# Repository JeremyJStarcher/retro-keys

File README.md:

# retro-keys
Retro Keyboards for emulators

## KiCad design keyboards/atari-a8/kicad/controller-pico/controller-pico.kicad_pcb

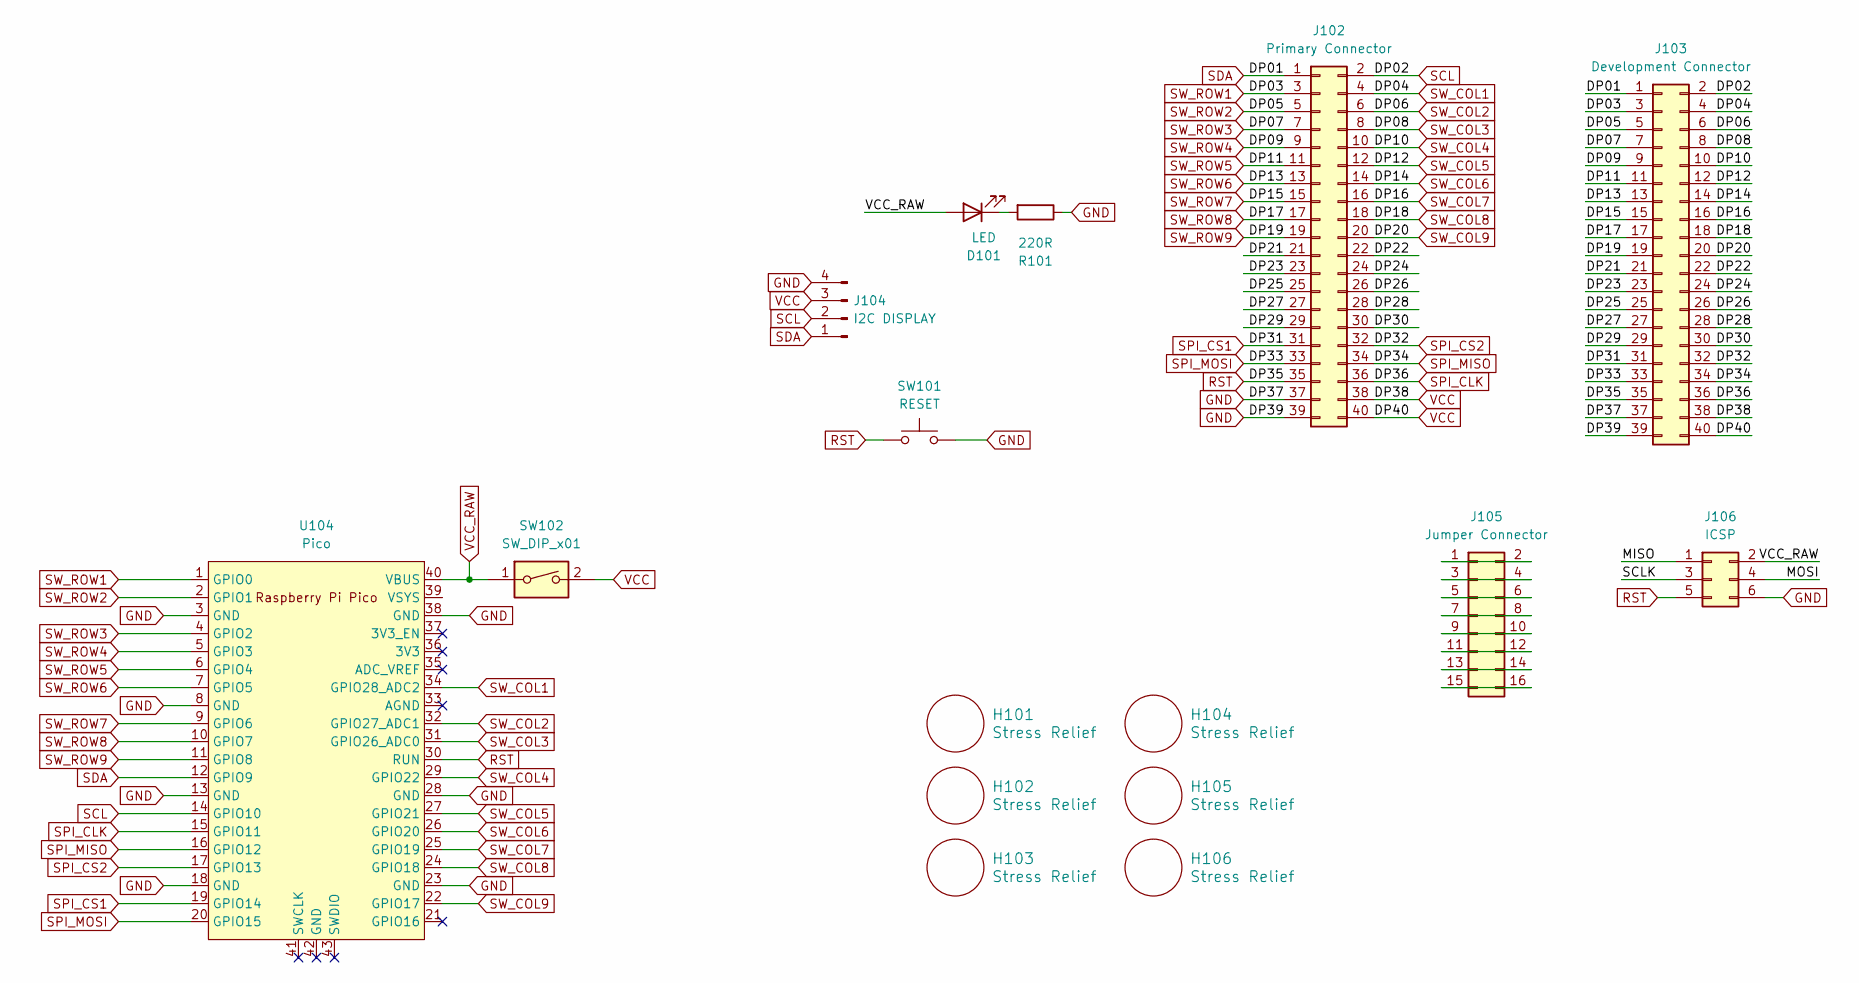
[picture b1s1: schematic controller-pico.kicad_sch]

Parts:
D101: LED; LED_D3.0mm
H101, H102, H103, H104, H105, H106: Stress Relief; MountingHole_2.7mm
J102: Primary Connector; PinHeader_2x20_P2.54mm_Vertical
J103: Development Connector; PinHeader_2x20_P2.54mm_Vertical
J104: I2C DISPLAY; PinHeader_1x04_P2.54mm_Horizontal
J105: Jumper Connector; PinHeader_2x08_P2.54mm_Vertical
J106: ICSP; PinHeader_2x03_P2.54mm_Vertical
R101: 220R; Resistor-Hybrid
SW101: RESET; SW_PUSH_6mm
SW102: SW_DIP_x01; SW_DIP_SPSTx01_Slide_9.78x4.72mm_W7.62mm_P2.54mm
U104: Pico; RPi_Pico_SMD_TH

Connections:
/DP21: J102.21, J103.21
/DP22: J102.22, J103.22
/DP23: J102.23, J103.23
/DP24: J102.24, J103.24
/DP25: J102.25, J103.25
/DP26: J102.26, J103.26
/DP27: J102.27, J103.27
/DP28: J102.28, J103.28
/DP29: J102.29, J103.29
/DP30: J102.30, J103.30
/MISO: J106.1
/MOSI: J106.4
/SCLK: J106.3
GND: J102.37, J102.39, J103.37, J103.39, J104.4, J106.6, R101.1, SW101.2, U104.3 (GND), U104.8 (GND), U104.13 (GND), U104.18 (GND), U104.23 (GND), U104.28 (GND), U104.38 (GND)
unnamed: D101.1 (K), R101.2
unnamed: J105.1, J105.2
unnamed: J105.3, J105.4
unnamed: J105.5, J105.6
unnamed: J105.7, J105.8
unnamed: J105.9, J105.10
unnamed: J105.11, J105.12
unnamed: J105.13, J105.14
unnamed: J105.15, J105.16
RST: J102.35, J103.35, J106.5, SW101.1, U104.30 (RUN)
SCL: J102.2, J103.2, J104.2, U104.14 (GPIO10)
SDA: J102.1, J103.1, J104.1, U104.12 (GPIO9)
SPI_CLK: J102.36, J103.36, U104.15 (GPIO11)
SPI_CS1: J102.31, J103.31, U104.19 (GPIO14)
SPI_CS2: J102.32, J103.32, U104.17 (GPIO13)
SPI_MISO: J102.34, J103.34, U104.16 (GPIO12)
SPI_MOSI: J102.33, J103.33, U104.20 (GPIO15)
SW_COL1: J102.4, J103.4, U104.34 (GPIO28_ADC2)
SW_COL2: J102.6, J103.6, U104.32 (GPIO27_ADC1)
SW_COL3: J102.8, J103.8, U104.31 (GPIO26_ADC0)
SW_COL4: J102.10, J103.10, U104.29 (GPIO22)
SW_COL5: J102.12, J103.12, U104.27 (GPIO21)
SW_COL6: J102.14, J103.14, U104.26 (GPIO20)
SW_COL7: J102.16, J103.16, U104.25 (GPIO19)
SW_COL8: J102.18, J103.18, U104.24 (GPIO18)
SW_COL9: J102.20, J103.20, U104.22 (GPIO17)
SW_ROW1: J102.3, J103.3, U104.1 (GPIO0)
SW_ROW2: J102.5, J103.5, U104.2 (GPIO1)
SW_ROW3: J102.7, J103.7, U104.4 (GPIO2)
SW_ROW4: J102.9, J103.9, U104.5 (GPIO3)
SW_ROW5: J102.11, J103.11, U104.6 (GPIO4)
SW_ROW6: J102.13, J103.13, U104.7 (GPIO5)
SW_ROW7: J102.15, J103.15, U104.9 (GPIO6)
SW_ROW8: J102.17, J103.17, U104.10 (GPIO7)
SW_ROW9: J102.19, J103.19, U104.11 (GPIO8)
VCC: J102.38, J102.40, J103.38, J103.40, J104.3, SW102.2
VCC_RAW: D101.2 (A), J106.2, SW102.1, U104.40 (VBUS)

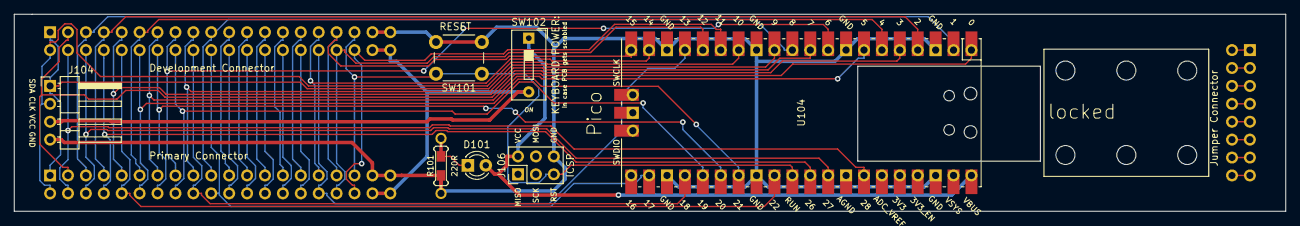
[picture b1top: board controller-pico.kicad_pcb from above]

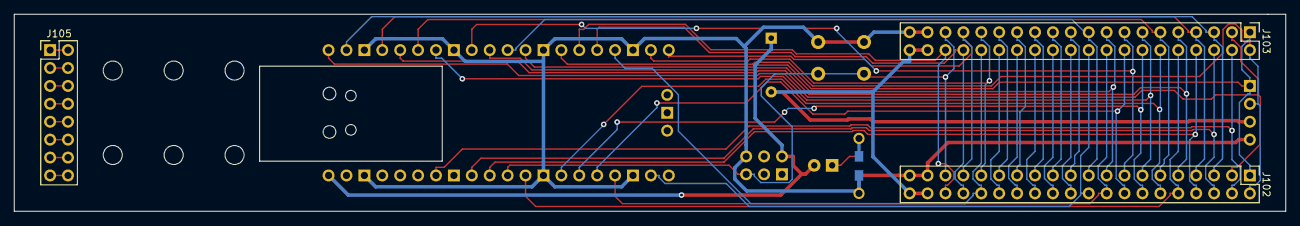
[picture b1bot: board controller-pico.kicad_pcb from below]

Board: 2 copper layers, 180.3 x 27.9 mm, 16 parts (3 on the bottom side), 48 nets.

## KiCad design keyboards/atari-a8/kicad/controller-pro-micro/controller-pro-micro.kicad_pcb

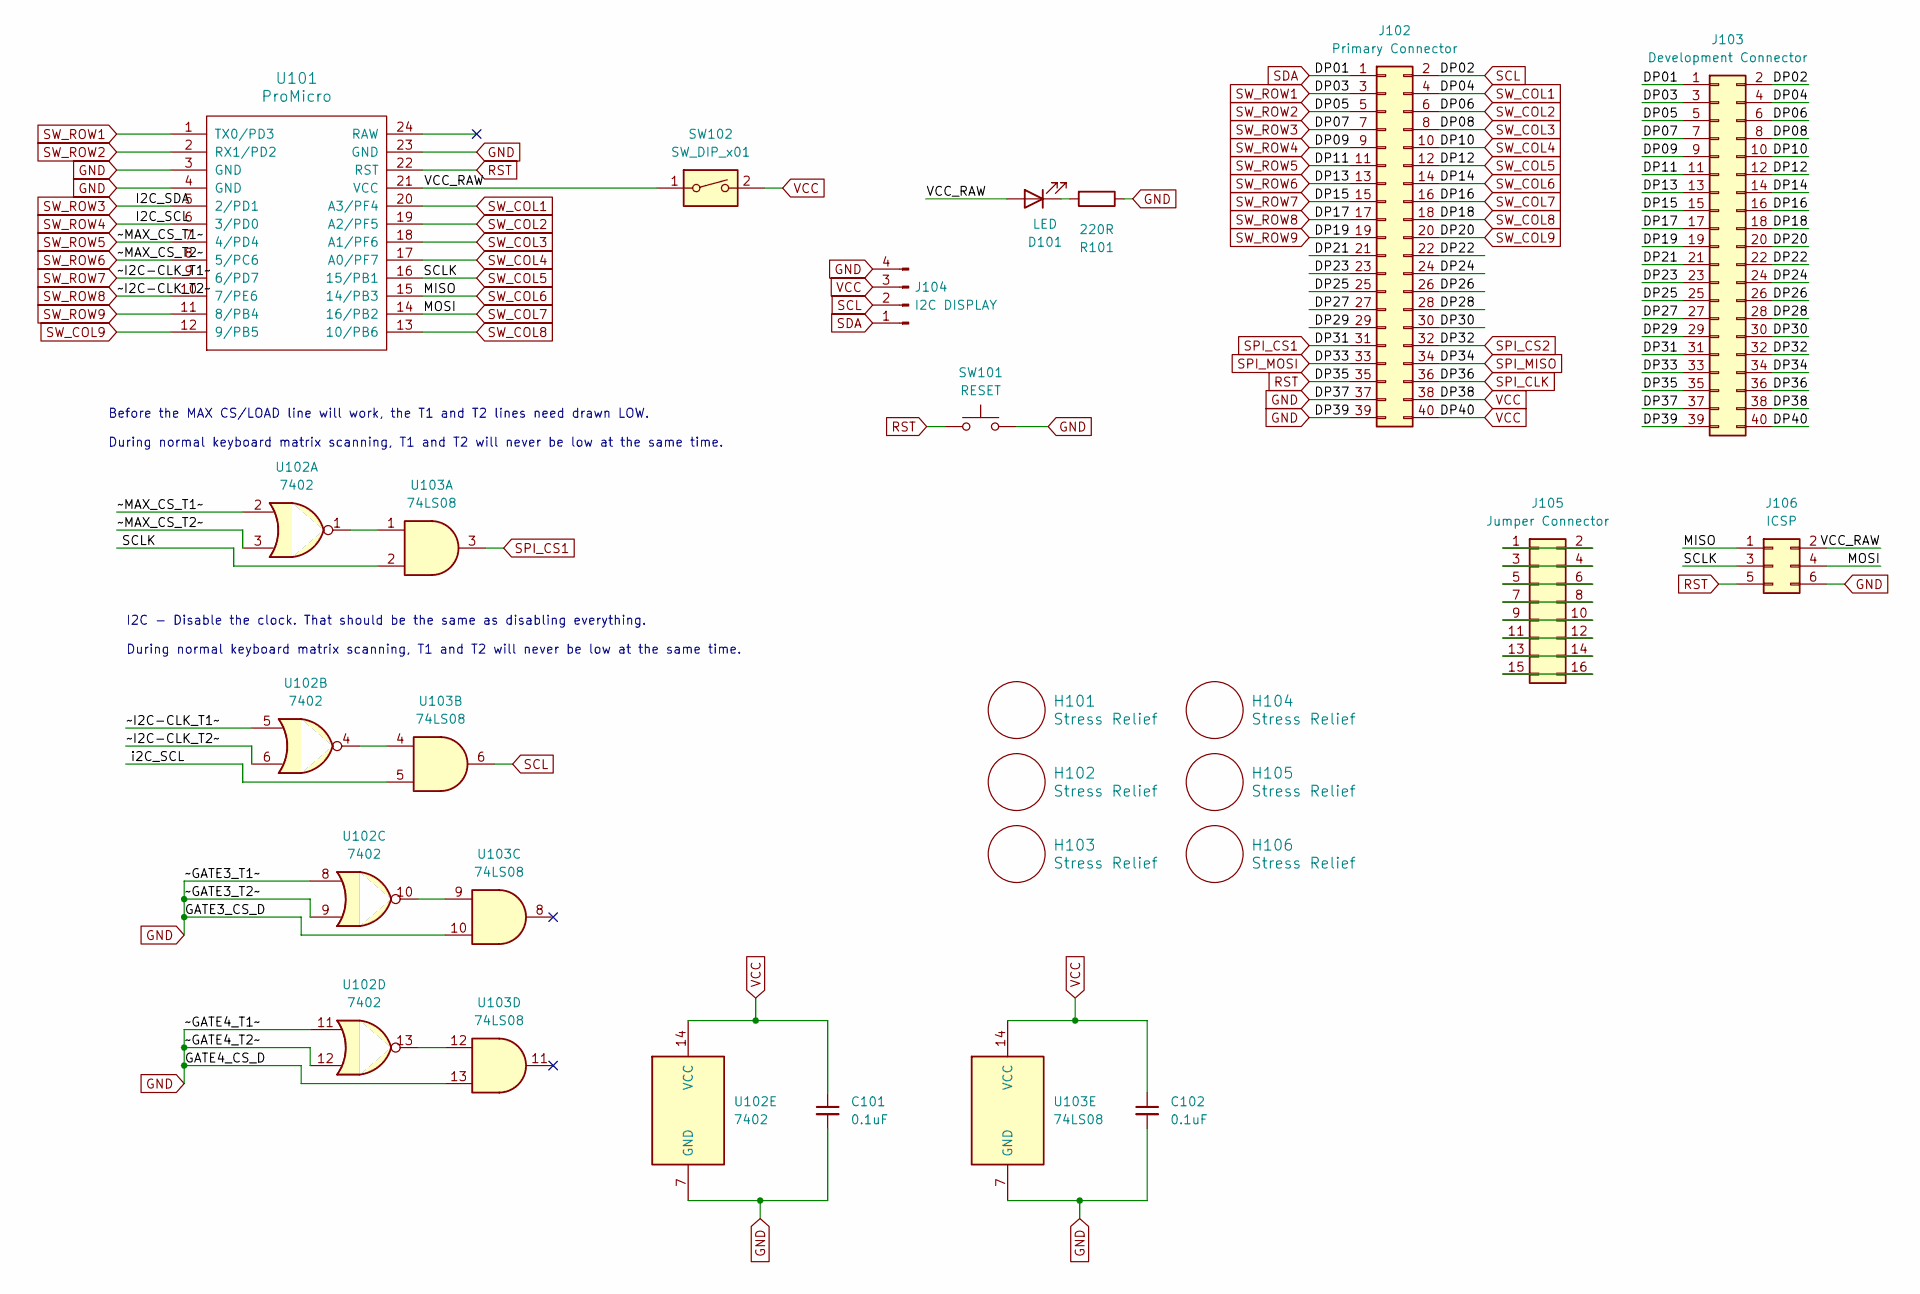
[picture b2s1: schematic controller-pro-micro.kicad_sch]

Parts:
C101, C102: 0.1uF; C_Axial_L3.8mm_D2.6mm_P7.50mm_Horizontal
D101: LED; LED_D3.0mm
H101, H102, H103, H104, H105, H106: Stress Relief; MountingHole_2.7mm
J102: Primary Connector; PinHeader_2x20_P2.54mm_Vertical
J103: Development Connector; PinHeader_2x20_P2.54mm_Vertical
J104: I2C DISPLAY; PinHeader_1x04_P2.54mm_Horizontal
J105: Jumper Connector; PinHeader_2x08_P2.54mm_Vertical
J106: ICSP; PinHeader_2x03_P2.54mm_Vertical
R101: 220R; Resistor-Hybrid
SW101: RESET; SW_PUSH_6mm
SW102: SW_DIP_x01; SW_DIP_SPSTx01_Slide_9.78x4.72mm_W7.62mm_P2.54mm
U101: ProMicro
U102: 7402; DIP-14_W7.62mm_Socket
U103: 74LS08; DIP-14_W7.62mm_Socket

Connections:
/DP21: J102.21, J103.21
/DP22: J102.22, J103.22
/DP23: J102.23, J103.23
/DP24: J102.24, J103.24
/DP25: J102.25, J103.25
/DP26: J102.26, J103.26
/DP27: J102.27, J103.27
/DP28: J102.28, J103.28
/DP29: J102.29, J103.29
/DP30: J102.30, J103.30
/VCC_RAW: D101.2 (A), J106.2, SW102.1, U101.21 (VCC)
/i2C_SCL: U103.5
GND: C101.2, C102.2, J102.37, J102.39, J103.37, J103.39, J104.4, J106.6, R101.1, SW101.2, U101.3 (GND), U101.4 (GND), U101.23 (GND), U102.7 (GND), U102.8, U102.9, U102.11, U102.12, U103.7 (GND), U103.10, U103.13
unnamed: D101.1 (K), R101.2
unnamed: J105.1, J105.2
unnamed: J105.3, J105.4
unnamed: J105.5, J105.6
unnamed: J105.7, J105.8
unnamed: J105.9, J105.10
unnamed: J105.11, J105.12
unnamed: J105.13, J105.14
unnamed: J105.15, J105.16
unnamed: U102.1, U103.1
unnamed: U102.4, U103.4
unnamed: U102.10, U103.9
unnamed: U102.13, U103.12
RST: J102.35, J103.35, J106.5, SW101.1, U101.22 (RST)
SCL: J102.2, J103.2, J104.2, U103.6
SDA: J102.1, J103.1, J104.1
SPI_CLK: J102.36, J103.36
SPI_CS1: J102.31, J103.31, U103.3
SPI_CS2: J102.32, J103.32
SPI_MISO: J102.34, J103.34
SPI_MOSI: J102.33, J103.33
SW_COL1: J102.4, J103.4, U101.20 (A3/PF4)
SW_COL2: J102.6, J103.6, U101.19 (A2/PF5)
SW_COL3: J102.8, J103.8, U101.18 (A1/PF6)
SW_COL4: J102.10, J103.10, U101.17 (A0/PF7)
SW_COL5: J102.12, J103.12, J106.3, U101.16 (15/PB1), U103.2
SW_COL6: J102.14, J103.14, J106.1, U101.15 (14/PB3)
SW_COL7: J102.16, J103.16, J106.4, U101.14 (16/PB2)
SW_COL8: J102.18, J103.18, U101.13 (10/PB6)
SW_COL9: J102.20, J103.20, U101.12 (9/PB5)
SW_ROW1: J102.3, J103.3, U101.1 (TX0/PD3)
SW_ROW2: J102.5, J103.5, U101.2 (RX1/PD2)
SW_ROW3: J102.7, J103.7, U101.5 (2/PD1)
SW_ROW4: J102.9, J103.9, U101.6 (3/PD0)
SW_ROW5: J102.11, J103.11, U101.7 (4/PD4), U102.2
SW_ROW6: J102.13, J103.13, U101.8 (5/PC6), U102.3
SW_ROW7: J102.15, J103.15, U101.9 (6/PD7), U102.5
SW_ROW8: J102.17, J103.17, U101.10 (7/PE6), U102.6
SW_ROW9: J102.19, J103.19, U101.11 (8/PB4)
VCC: C101.1, C102.1, J102.38, J102.40, J103.38, J103.40, J104.3, SW102.2, U102.14 (VCC), U103.14 (VCC)

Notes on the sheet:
I2C - Disable the clock. That should be the same as disabling everything. During normal keyboard matrix scanning, T1 and T2 will never be low at the same time.
Before the MAX CS/LOAD line will work, the T1 and T2 lines need drawn LOW. During normal keyboard matrix scanning, T1 and T2 will never be low at the same time.

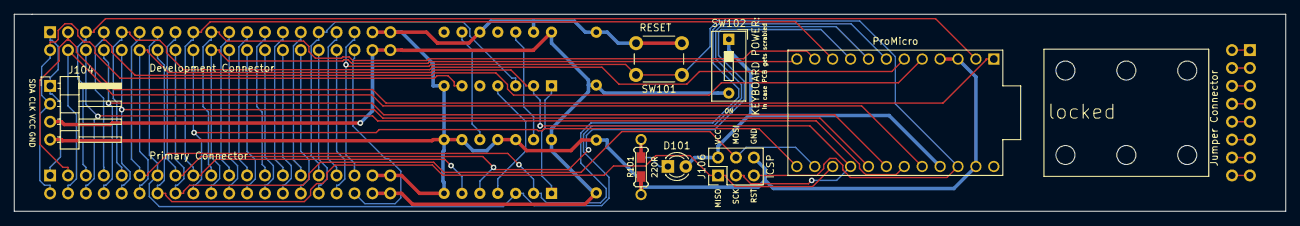
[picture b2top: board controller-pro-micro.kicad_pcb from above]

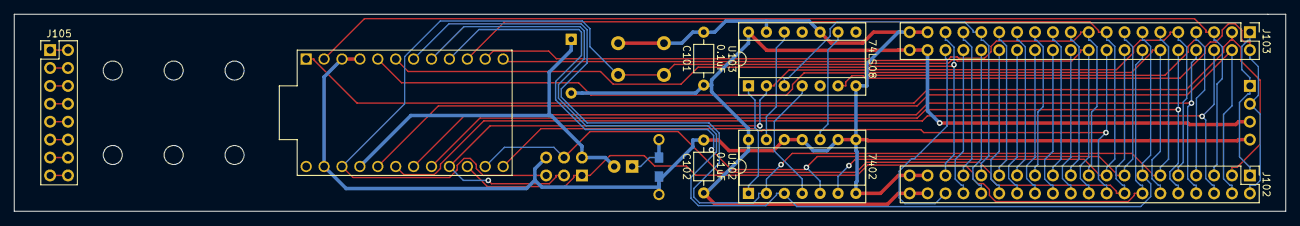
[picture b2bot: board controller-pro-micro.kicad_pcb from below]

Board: 2 copper layers, 180.3 x 27.9 mm, 20 parts (7 on the bottom side), 52 nets.

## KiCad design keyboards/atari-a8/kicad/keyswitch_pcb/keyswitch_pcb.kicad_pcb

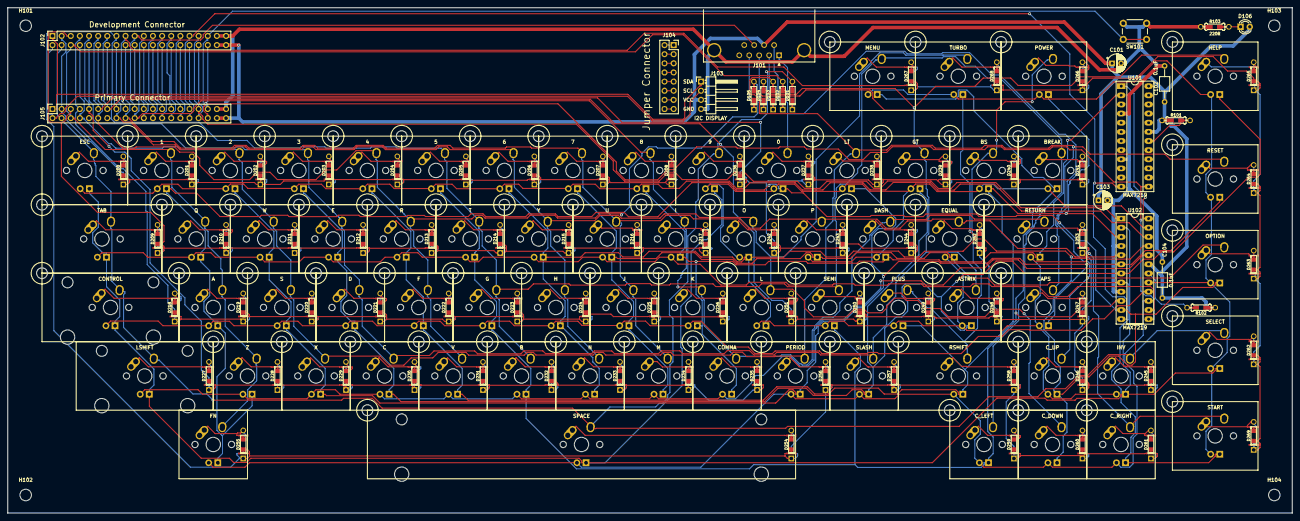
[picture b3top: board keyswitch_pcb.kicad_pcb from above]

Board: 2 copper layers, 357.2 x 140.5 mm, 165 parts (0 on the bottom side), 142 nets.

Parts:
C101, C103: 47uF; CP_Radial_D5.0mm_P2.50mm
C102, C104: 0.1uF; C_Axial_L3.8mm_D2.6mm_P10.00mm_Horizontal
D101: JS1_UP; Diode-dual
D102: JS1_TRIG; Diode-dual
D103: JS1_DOWN; Diode-dual
D104: JS1_LEFT; Diode-dual
D105: JS1_RIGHT; Diode-dual
D106: LED; LED_D3.0mm
D200: ESC; Diode-dual
D201: 1; Diode-dual
D202: 2; Diode-dual
D203: 3; Diode-dual
D204: 4; Diode-dual
D205: 5; Diode-dual
D206: 6; Diode-dual
D207: 7; Diode-dual
D208: 8; Diode-dual
D209: TAB; Diode-dual
D210: Q; Diode-dual
D211: W; Diode-dual
D212: E; Diode-dual
D213: R; Diode-dual
D214: T; Diode-dual
D215: Y; Diode-dual
D216: U; Diode-dual
D217: I; Diode-dual
D218: CONTROL; Diode-dual
D219: A; Diode-dual
D220: S; Diode-dual
D221: D; Diode-dual
D222: F; Diode-dual
D223: G; Diode-dual
D224: H; Diode-dual
D225: J; Diode-dual
D226: K; Diode-dual
D227: LSHIFT; Diode-dual
D228: Z; Diode-dual
D229: X; Diode-dual
D230: C; Diode-dual
D231: V; Diode-dual
D232: B; Diode-dual
D233: N; Diode-dual
D234: M; Diode-dual
D235: COMMA; Diode-dual
D236: 9; Diode-dual
D237: 0; Diode-dual
D238: LT; Diode-dual
D239: GT; Diode-dual
D240: BS; Diode-dual
D241: BREAK; Diode-dual
D242: O; Diode-dual
D243: P; Diode-dual
D244: DASH; Diode-dual
D245: INV; Diode-dual
D246: C_UP; Diode-dual
D247: CAPS; Diode-dual
D248: ASTRIX; Diode-dual
D249: PLUS; Diode-dual
D250: SEMI; Diode-dual
D251: L; Diode-dual
D252: EQUAL; Diode-dual
D253: RETURN; Diode-dual
D254: SPACE; Diode-dual
D255: FN; Diode-dual
D256: PERIOD; Diode-dual
D257: SLASH; Diode-dual
D258: RSHIFT; Diode-dual
D259: C_LEFT; Diode-dual
D260: C_DOWN; Diode-dual
D261: C_RIGHT; Diode-dual
D262: SELECT; Diode-dual
D263: OPTION; Diode-dual
D264: RESET; Diode-dual
D265: HELP; Diode-dual
D266: POWER; Diode-dual
D267: MENU; Diode-dual
D268: TURBO; Diode-dual
D269: START; Diode-dual
H101, H102, H103, H104: MountingHole; MountingHole_3.2mm_M3
J101: PLAYER 1; DSUB-9_Male_Horizontal_P2.77x2.84mm_EdgePinOffset9.90mm_Hou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
J102: Development Connector; PinSocket_2x20_P2.54mm_Vertical
J103: I2C DISPLAY; PinHeader_1x04_P2.54mm_Horizontal
J104: Jumper Connector; PinSocket_2x08_P2.54mm_Vertical
J105: Primary Connector; PinSocket_2x20_P2.54mm_Vertical
R101, R102: 22K; Resistor-Hybrid
R103: 220R; Resistor-Hybrid
SW101: RESET; SW_PUSH_6mm
SW200: ESC; MX-1.25U
SW201: 1; MX-1U
SW202: 2; MX-1U
SW203: 3; MX-1U
SW204: 4; MX-1U
SW205: 5; MX-1U
SW206: 6; MX-1U
SW207: 7; MX-1U
SW208: 8; MX-1U
SW209: TAB; MX-1.75U
SW210: Q; MX-1U
SW211: W; MX-1U
SW212: E; MX-1U
SW213: R; MX-1U
SW214: T; MX-1U
SW215: Y; MX-1U
SW216: U; MX-1U
SW217: I; MX-1U
SW218: CONTROL; MX-2U
SW219: A; MX-1U
SW220: S; MX-1U
SW221: D; MX-1U
SW222: F; MX-1U
SW223: G; MX-1U
SW224: H; MX-1U
SW225: J; MX-1U
SW226: K; MX-1U
SW227: LSHIFT; MX-2U
SW228: Z; MX-1U
SW229: X; MX-1U
SW230: C; MX-1U
SW231: V; MX-1U
SW232: B; MX-1U
SW233: N; MX-1U
SW234: M; MX-1U
SW235: COMMA; MX-1U
SW236: 9; MX-1U
SW237: 0; MX-1U
SW238: LT; MX-1U
SW239: GT; MX-1U
SW240: BS; MX-1U
SW241: BREAK; MX-1U
SW242: O; MX-1U
SW243: P; MX-1U
SW244: DASH; MX-1U
SW245: INV; MX-1U
SW246: C_UP; MX-1U
SW247: CAPS; MX-1.25U
SW248: ASTRIX; MX-1U
SW249: PLUS; MX-1U
SW250: SEMI; MX-1U
SW251: L; MX-1U
SW252: EQUAL; MX-1U
SW253: RETURN; MX-1.5U
SW254: SPACE; MX-6.25U
SW255: FN; MX-1U
SW256: PERIOD; MX-1U
SW257: SLASH; MX-1U
SW258: RSHIFT; MX-1.75U
SW259: C_LEFT; MX-1U
SW260: C_DOWN; MX-1U
SW261: C_RIGHT; MX-1U
SW262: SELECT; MX-1.25U
SW263: OPTION; MX-1.25U
SW264: RESET; MX-1.25U
SW265: HELP; MX-1.25U
SW266: POWER; MX-1.25U
SW267: MENU; MX-1.25U
SW268: TURBO; MX-1.25U
SW269: START; MX-1.25U
U101, U102: MAX7219; DIP-24_W7.62mm_Socket_LongPads

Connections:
/DP21: J102.21, J105.21
/DP22: J102.22, J105.22
/DP23: J102.23, J105.23
/DP24: J102.24, J105.24
/DP25: J102.25, J105.25
/DP26: J102.26, J105.26
/DP27: J102.27, J105.27
/DP28: J102.28, J105.28
/DP29: J102.29, J105.29
/DP30: J102.30, J105.30
/SPI_D2: U101.1 (DIN), U102.24 (DOUT)
GND: C101.2, C102.2, C103.2, C104.2, J101.0 (GND), J102.37, J102.39, J103.4, J105.37, J105.39, R103.1, SW101.2, U101.4 (GND), U101.9 (GND), U102.4 (GND), U102.9 (GND)
LED_COL1: SW200.4, SW209.4, SW218.4, SW227.4, SW236.4, SW245.4, SW254.4, SW262.4, U102.2 (DIG_0)
LED_COL2: SW201.4, SW210.4, SW219.4, SW228.4, SW237.4, SW246.4, SW255.4, SW263.4, U102.11 (DIG_1)
LED_COL3: SW202.4, SW211.4, SW220.4, SW229.4, SW238.4, SW247.4, SW256.4, SW264.4, U102.6 (DIG_2)
LED_COL4: SW203.4, SW212.4, SW221.4, SW230.4, SW239.4, SW248.4, SW257.4, SW265.4, U102.7 (DIG_3)
LED_COL5: SW204.4, SW213.4, SW222.4, SW231.4, SW240.4, SW249.4, SW258.4, SW266.4, U102.3 (DIG_4)
LED_COL6: SW205.4, SW214.4, SW223.4, SW232.4, SW241.4, SW250.4, SW259.4, SW267.4, U102.10 (DIG_5)
LED_COL7: SW206.4, SW215.4, SW224.4, SW233.4, SW242.4, SW251.4, SW260.4, SW268.4, U102.5 (DIG_6)
LED_COL8: SW207.4, SW216.4, SW225.4, SW234.4, SW243.4, SW252.4, SW261.4, SW269.4, U102.8 (DIG_7)
LED_COL9: SW208.4, SW217.4, SW226.4, SW235.4, SW244.4, SW253.4, U101.2 (DIG_0)
LED_ROW1: SW200.3, SW201.3, SW202.3, SW203.3, SW204.3, SW205.3, SW206.3, SW207.3, SW208.3, U102.22 (SEG_DP)
LED_ROW2: SW209.3, SW210.3, SW211.3, SW212.3, SW213.3, SW214.3, SW215.3, SW216.3, SW217.3, U102.14 (SEG_A)
LED_ROW3: SW218.3, SW219.3, SW220.3, SW221.3, SW222.3, SW223.3, SW224.3, SW225.3, SW226.3, U102.16 (SEG_B)
LED_ROW4: SW227.3, SW228.3, SW229.3, SW230.3, SW231.3, SW232.3, SW233.3, SW234.3, SW235.3, U102.20 (SEG_C)
LED_ROW5: SW236.3, SW237.3, SW238.3, SW239.3, SW240.3, SW241.3, SW242.3, SW243.3, SW244.3, U102.23 (SEG_D)
LED_ROW6: SW245.3, SW246.3, SW247.3, SW248.3, SW249.3, SW250.3, SW251.3, SW252.3, SW253.3, U102.21 (SEG_E)
LED_ROW7: SW254.3, SW255.3, SW256.3, SW257.3, SW258.3, SW259.3, SW260.3, SW261.3, U102.15 (SEG_F)
LED_ROW8: SW262.3, SW263.3, SW264.3, SW265.3, SW266.3, SW267.3, SW268.3, SW269.3, U102.17 (SEG_G)
unnamed: D101.1 (K), J101.1
unnamed: D102.1 (K), J101.6
unnamed: D103.1 (K), J101.2
unnamed: D104.1 (K), J101.3
unnamed: D105.1 (K), J101.4
unnamed: D106.1 (K), R103.2
unnamed: D200.2 (A), SW200.1
unnamed: D201.2 (A), SW201.1
unnamed: D202.2 (A), SW202.1
unnamed: D203.2 (A), SW203.1
unnamed: D204.2 (A), SW204.1
unnamed: D205.2 (A), SW205.1
unnamed: D206.2 (A), SW206.1
unnamed: D207.2 (A), SW207.1
unnamed: D208.2 (A), SW208.1
unnamed: D209.2 (A), SW209.1
unnamed: D210.2 (A), SW210.1
unnamed: D211.2 (A), SW211.1
unnamed: D212.2 (A), SW212.1
unnamed: D213.2 (A), SW213.1
unnamed: D214.2 (A), SW214.1
unnamed: D215.2 (A), SW215.1
unnamed: D216.2 (A), SW216.1
unnamed: D217.2 (A), SW217.1
unnamed: D218.2 (A), SW218.1
unnamed: D219.2 (A), SW219.1
unnamed: D220.2 (A), SW220.1
unnamed: D221.2 (A), SW221.1
unnamed: D222.2 (A), SW222.1
unnamed: D223.2 (A), SW223.1
unnamed: D224.2 (A), SW224.1
unnamed: D225.2 (A), SW225.1
unnamed: D226.2 (A), SW226.1
unnamed: D227.2 (A), SW227.1
unnamed: D228.2 (A), SW228.1
unnamed: D229.2 (A), SW229.1
unnamed: D230.2 (A), SW230.1
unnamed: D231.2 (A), SW231.1
unnamed: D232.2 (A), SW232.1
unnamed: D233.2 (A), SW233.1
unnamed: D234.2 (A), SW234.1
unnamed: D235.2 (A), SW235.1
unnamed: D236.2 (A), SW236.1
unnamed: D237.2 (A), SW237.1
unnamed: D238.2 (A), SW238.1
unnamed: D239.2 (A), SW239.1
unnamed: D240.2 (A), SW240.1
unnamed: D241.2 (A), SW241.1
unnamed: D242.2 (A), SW242.1
unnamed: D243.2 (A), SW243.1
unnamed: D244.2 (A), SW244.1
unnamed: D245.2 (A), SW245.1
unnamed: D246.2 (A), SW246.1
unnamed: D247.2 (A), SW247.1
unnamed: D248.2 (A), SW248.1
unnamed: D249.2 (A), SW249.1
unnamed: D250.2 (A), SW250.1
unnamed: D251.2 (A), SW251.1
unnamed: D252.2 (A), SW252.1
unnamed: D253.2 (A), SW253.1
unnamed: D254.2 (A), SW254.1
unnamed: D255.2 (A), SW255.1
unnamed: D256.2 (A), SW256.1
unnamed: D257.2 (A), SW257.1
unnamed: D258.2 (A), SW258.1
unnamed: D259.2 (A), SW259.1
unnamed: D260.2 (A), SW260.1
unnamed: D261.2 (A), SW261.1
unnamed: D262.2 (A), SW262.1
unnamed: D263.2 (A), SW263.1
unnamed: D264.2 (A), SW264.1
unnamed: D265.2 (A), SW265.1
unnamed: D266.2 (A), SW266.1
unnamed: D267.2 (A), SW267.1
unnamed: D268.2 (A), SW268.1
unnamed: D269.2 (A), SW269.1
unnamed: J104.1, J104.2
unnamed: J104.3, J104.4
unnamed: J104.5, J104.6
unnamed: J104.7, J104.8
unnamed: J104.9, J104.10
unnamed: J104.11, J104.12
unnamed: J104.13, J104.14
unnamed: J104.15, J104.16
unnamed: R101.2, U101.18 (ISET)
unnamed: R102.2, U102.18 (ISET)
RST: J102.35, J105.35, SW101.1
SCL: J102.2, J103.2, J105.2
SDA: J102.1, J103.1, J105.1
SPI_CLK: J102.36, J105.36, U101.13 (CLK), U102.13 (CLK)
SPI_CS1: J102.31, J105.31, U101.12 (LOAD), U102.12 (LOAD)
SPI_CS2: J102.32, J105.32
SPI_MISO: J102.34, J105.34
SPI_MOSI: J102.33, J105.33, U102.1 (DIN)
SW_COL1: D101.2 (A), J102.4, J105.4, SW200.2, SW209.2, SW218.2, SW227.2, SW236.2, SW245.2, SW254.2, SW262.2
SW_COL2: D102.2 (A), J102.6, J105.6, SW201.2, SW210.2, SW219.2, SW228.2, SW237.2, SW246.2, SW255.2, SW263.2
SW_COL3: D103.2 (A), J102.8, J105.8, SW202.2, SW211.2, SW220.2, SW229.2, SW238.2, SW247.2, SW256.2, SW264.2
SW_COL4: D104.2 (A), J102.10, J105.10, SW203.2, SW212.2, SW221.2, SW230.2, SW239.2, SW248.2, SW257.2, SW265.2
SW_COL5: D105.2 (A), J102.12, J105.12, SW204.2, SW213.2, SW222.2, SW231.2, SW240.2, SW249.2, SW258.2, SW266.2
SW_COL6: J102.14, J105.14, SW205.2, SW214.2, SW223.2, SW232.2, SW241.2, SW250.2, SW259.2, SW267.2
SW_COL7: J102.16, J105.16, SW206.2, SW215.2, SW224.2, SW233.2, SW242.2, SW251.2, SW260.2, SW268.2
SW_COL8: J102.18, J105.18, SW207.2, SW216.2, SW225.2, SW234.2, SW243.2, SW252.2, SW261.2, SW269.2
SW_COL9: J102.20, J105.20, SW208.2, SW217.2, SW226.2, SW235.2, SW244.2, SW253.2
SW_ROW1: D200.1 (K), D201.1 (K), D202.1 (K), D203.1 (K), D204.1 (K), D205.1 (K), D206.1 (K), D207.1 (K), D208.1 (K), J102.3, J105.3
SW_ROW2: D209.1 (K), D210.1 (K), D211.1 (K), D212.1 (K), D213.1 (K), D214.1 (K), D215.1 (K), D216.1 (K), D217.1 (K), J102.5, J105.5
SW_ROW3: D218.1 (K), D219.1 (K), D220.1 (K), D221.1 (K), D222.1 (K), D223.1 (K), D224.1 (K), D225.1 (K), D226.1 (K), J102.7, J105.7
SW_ROW4: D227.1 (K), D228.1 (K), D229.1 (K), D230.1 (K), D231.1 (K), D232.1 (K), D233.1 (K), D234.1 (K), D235.1 (K), J102.9, J105.9
SW_ROW5: D236.1 (K), D237.1 (K), D238.1 (K), D239.1 (K), D240.1 (K), D241.1 (K), D242.1 (K), D243.1 (K), D244.1 (K), J102.11, J105.11
SW_ROW6: D245.1 (K), D246.1 (K), D247.1 (K), D248.1 (K), D249.1 (K), D250.1 (K), D251.1 (K), D252.1 (K), D253.1 (K), J102.13, J105.13
SW_ROW7: D254.1 (K), D255.1 (K), D256.1 (K), D257.1 (K), D258.1 (K), D259.1 (K), D260.1 (K), D261.1 (K), J102.15, J105.15
SW_ROW8: D262.1 (K), D263.1 (K), D264.1 (K), D265.1 (K), D266.1 (K), D267.1 (K), D268.1 (K), D269.1 (K), J102.17, J105.17
SW_ROW9: J101.8, J102.19, J105.19
VCC: C101.1, C102.1, C103.1, C104.1, D106.2 (A), J101.7, J102.38, J102.40, J103.3, J105.38, J105.40, R101.1, R102.1, U101.19 (V+), U102.19 (V+)

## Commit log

2022-12-25 added first phase of reworking python tooling
2022-12-25 Moved python files
2022-12-25 Moved over process_keyboard and began to update to new API
2022-12-25 Added keycap generator
2022-12-25 Added kicad-lib
2022-12-25 Re-enabled more features of process keyboard
2022-12-25 process_keyboard at feature parity with old version
2022-12-25 Added Atari-A8 PCB
2022-12-25 Added script to call free-router
2022-12-26 Made a bunch of paths and config settings a config object in prep for splitting out the Atari-a8 into its own file.
2022-12-26 More cleanup of the PCB traces.
2022-12-26 Pulled out the 'atari_a8.py' code
2022-12-26 Added SOD-123 diode models to PCB
2022-12-26 Don't need the '__main__' code
2022-12-26 code reformat
2022-12-26 Replaced unix command line tools to convert stl to wrl with a python script.
2022-12-26 Added better comments.
2022-12-26 Added Atari keyboard graphics.
2022-12-26 Cleaned up some more trace.
2022-12-26 Changed Atari keycap colour again
2022-12-26 Started to collect C64 keycap info
2022-12-26 No longer need standoff holes as part of the schematic. Added automatically by the script.
2022-12-26 Used new standoff holes and more track cleanup work.
2022-12-26 Moved KeyV2 to be used commonly
2022-12-26 Created some keycaps just to generate web page legends with
2022-12-27 Added script header
2022-12-27 Started working on the README
2022-12-27 Fixed README.md issues
2023-01-07 More rework of designing a printable key layout
2023-01-07 REdirected to info.json file.
2023-01-08 Started to work on case design
2023-01-08 Fixed some autolayout for resin prints.
2023-01-08 More work on case design done.
2023-01-08 Fixed some standoff spacing
    Added labels to the bounding boxes and noticed that the manually
    positioned standoffs were in the wrong y location. Fixed that.
2023-01-08 Fixed it for real
2023-01-08 Cleaned up case design quite a bit
2023-01-09 Moved the last hard-coded SCAD module out of the py file
    and increased the text of bounding boxes by limiting it to
    just the first two lettes..
2023-01-12 Added the ability to slice the case into smaller pieces.
2023-01-14 Added countersunk case holes
2023-01-14 Created directory just for test-related data
2023-01-14 Started to work on qmk and kle convert
2023-01-15 Get the QMK list in the order needed for the KLE
2023-01-23 Added code to auto-generate the keyboard and split it properly.
2023-01-23 Added a two-part case as well.
2023-08-11 Restoring load files.
2023-08-11 Copied over test directory
2023-08-11 Added 3d models
2023-08-11 Atari keyboard
2023-08-11 C64/VIC20 keyboard
2023-08-11 Keycap generator
2023-08-11 Added the rest of the packages
2023-08-11 Added a cleaner start routine
2023-08-11 Resolved issue where keyboard script would not run if the gerbers directory did not exist.
2023-08-11 Cleaned some some inconsistent handling of QMK file handling
2023-08-11 Got the make all keycaps working
2023-08-12 common_key_format now loads the QMK style keymap.
2023-08-12 Moved config settings directly to the config object rather than using a useless DTO
2023-08-12 renamed qmk2kle to qmk_tools
2023-08-12 Added the KLE tools and tests
2023-08-12 Got the code to convert from KLE to QMK positions correctly sorted out.
2023-08-13 Added running coverage tests.
2023-08-13 Fixed things
2023-08-13 No longer generate KLE 'raw' file that was needed in development.
2023-08-13 Shifted the code to use the keyboard_layout file more
2023-08-13 Added get_all_symbol_value_references and fixed tests broken by change of data files.
2023-08-13 Cleaned up some file handling
2023-08-14 No longer need access to the QMK matrix to identify designations for switches/diodes. Now read directly off the schematic.
2023-08-23 Lots of changes to generating the model files, including constant paths for sanity.
2023-08-23 Reactived the full build
2023-11-25 Bunch of work for doing an auto-layout for the keyboard schematic
2023-11-25 Symbols are now added to the schematic properly, but spacing and wiring isn't done.
2023-11-26 Added the MX_Alps_Hybrid schematic and footprint library
2023-11-26 Added the MX leds to the schematic updator
2023-11-26 Key switches and diodes rendered in the correct place
2023-11-27 Parts and wiring rendering on the schematic
    Switched most calculations over to decimal mode to keep the precision needed when calculating where wires went. Has the plus side of not littering up the s-expression files with "approximates" of the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
2023-11-27 Clean schematic
2023-11-27 All of the wires for the keyboard/led grid in place
2023-11-28 Added MUCH stronger typing rules to the data
2023-11-28 New schematic in place and parts dropped on PCB
2023-11-28 PCB parts arranged
2023-11-29 Correct key sizes placed, diodes located, various auto-drawn stuff removed from PCB
2023-11-29 3d models properly placed
2023-11-29 Wrapped up all the processing functions to use a single I/O and pass in most dependencies.
2023-11-29 Replace `float("inf")` and cleaned up BoundingBox constructor
2023-11-29 Cleaned up some PinPosition/Wire handling
2023-11-29 Added a MUCH needed ability to find a sub list by query
2023-11-29 Replaced a recursionDepth with a recursion level.
2023-11-30 Added more detailed information about wires and pins and what they belong to
2023-11-30 Removed some dead code calculations needed by the old keyswitch footprints
2023-11-30 More dead code removal
2023-12-01 Better handling of where to draw the global tag
2023-12-01 Removed the now unused wiretype
2023-12-01 Get all the wires for global tags drawn and removed for dead code
2023-12-01 All global labels rendered. MAX7219's added. PCB updaed
2023-12-02 Added command line options rather than modifying code for what features to run.
2023-12-02 Changed LSHIFT from 2.25U to 2U (more available)
2023-12-02 All grid items now on schematic, but may be flagged as do-not-install
2023-12-02 Added an option to dump the schematic in python format
2023-12-02 Removed the mounting holes and keepout zones for now
2023-12-02 Fixed joystick wiring
2023-12-03 Added some tweaks learned working on keyboard prototype
2023-12-03 Added the 16x2 LED option
2023-12-04 Re-arranged keys and layout for LCD screen
2023-12-04 Removed all traces of JS2_ since there can only be one joystick
2023-12-04 Fixed issue where diodes did not display in 3d view
2023-12-05 A bunch of changes to support the new layout
2023-12-07 White space cleanup
2023-12-07 Updated the requirements.txt to pick up a missing dependency.
2023-12-23 Added data sheets
2023-12-23 Added library to generate plates
2023-12-24 Laying out data to generate the plate
2023-12-25 Added a python script to generate plates
2024-01-05 New PCB layout with controller on a daughter board.
2024-01-12 Added generating the keyboard plate
2024-02-04 Renamed the Atari keyswitch PCB
2024-02-04 Added datasheets
2024-02-04 Cleaned up board layout some and re-added lost pinout diagram
2024-02-04 Reworked mounting holes and cleaned up labeling.
2024-02-04 Linted code. Gathered list of all mounting holes.
2024-02-05 Mounting hole data added to the case-position.scad file
2024-02-06 Renamed the pro-micro controller files
2024-02-06 Renamed the pro micro controller
2024-02-23 Rev2 board
2024-12-08 Bunch of deleting old dead files
2024-12-08 Prepped code to add a bambu-style 3MF file
2024-12-08 Added a Bambu specific export
2024-12-08 Put the graphics legend on the text color too.
2024-12-08 Did some cleanup and got rid of the boolean trap
2024-12-09 Added option to reverse color of the keys.
2024-12-10 Fixed no legend handling. Finished two-color rendering.
2025-02-09 Worked on keycaps quite a bit
2025-02-09 More slogging at keycaps
2025-02-17 More work to try to get a good set of keycaps printing
